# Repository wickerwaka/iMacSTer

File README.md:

# iMacSTer

The iMacSTer is an early 2000's Apple iMac G3 with a MiSTer FPGA multisystem emulator inside of it. It is intended to be a non-destructive modification so the iMac can be returned to it's original state if desired. The mainboard, drives and IO panel are removed and replace by custom hardware, but no cuts are made to the chassis and the new hardware connects to existing internal connections without the need for any soldering. That being said, I can make no guarantees about the long term implications of these modifications. The speakers are being driven by a different amplifier than they were intended for, the new hardware only uses the 5V output from a power supply which is expecting load on the 3.3V and 12V lines also, the monitor is being driven at a resolution higher than it was intended for, heat generation and dissipation characteristics have changed, etc, etc.

## Past Work
None of this would be possible without the work of Rocky Hill and others to reverse engineer the iMac internals and design custom hardware and software to interface with it. I would not have attempted this project if the [imac_g3_ivad_board_init](https://github.com/qbancoffee/imac_g3_ivad_board_init) project did not exist. My PCBs and software is all based on that work and I still use the down converter adaptor board from that project because there was no need to change it.

I also used the IO shield designs that @Diepzeevogel created as part of their [replacement parts project](https://github.com/Diepzeevogel/iMac-G3-replacement-parts) as the basis for my own IO shield. The fit and quality that they were able to achieve is beyond my own skills.

## Features
 * 2W x 2 Stereo amplifier
 * Dual headphone ports for two player fun
 * External volume control
 * 4 external USB ports
 * Built-in WiFi
 * Access to all MiSTer buttons and OSD
 * Sleek design for any modern home

[Other Random Photos](https://photos.app.goo.gl/XmcNqWLyWzHymW5z9)

## Assembly

## Main Board

The main board controls the whole system. It contains an I2S digital-to-analog audio converter, an audio amplifier and an Arduino Nano Every for controlling everything. It connects to the J20 connector inside the iMac which provides 5V to the microcontroller even when the system is powered down. The J20 port is also where the VGA signals are from the VGA connector on the board.

The amplifier is a Texas Instruments [TPA6021A4](https://www.ti.com/lit/ds/symlink/tpa6021a4.pdf) 2W Stereo amplifier. I picked this one because it was in the power range I needed, it supported a headphone mode, the volume level could be controlled by a microcontroller and it came in a through-hole package. That last point really limits the options since most amplifier ICs with similar features come in surface mount packages. When I started this project I had no experience designing PCBs or using surface mount components, so I was limiting myself to through-hole parts. The decoupling, biasing and filtering capacitors in the amplifier section are all directly copied from the reference schematics in the datasheet, with the exception of the output capacitors which I switch from 330uF to 2200uF in order to get more bass.

The amplifier output is connected to the speakers and headphones via two JST connectors. The iMac has two separate headphone ports on the front and each has their own headphone sense signal. These signals need to be OR'd together to determine whether the amplifier should be in single ended (headphone) mode or not. This is done by the arduino rather than a separate IC, which has the added advantage of allowing separate volume settings for speaker and headphone mode.

The audio input to the amplifier comes from the [UDA1334A](https://cdn-shop.adafruit.com/product-files/3678/UDA1334ATS.pdf) [breakout board](https://www.adafruit.com/product/3678) from Adafruit. The UDA1334A decodes the I2S audio data from the MiSTer and converts it to an analog signal. I had assumed the output capacitors on the breakout board would block DC into the amplifier so an earlier version of the board did not have any capacitors protecting the input. That assumption cost me a pair of speakers, they literally ripped themselves apart.

The arduino controls the system power, the CRT configuration, the amplifier, the buttons and LEDs on the case and the three standard buttons on the MiSTer. I considered using an ATmega microcontroller directly instead of the Nano Every, however the Nano packs a lot of features into a small space. I want the convenience of a USB port without having to worry about whether I've hooked it all up correctly. 

iMac video hardware requires a special initialization sequence to be sent via I2C before it will power on the CRT and start displaying an image ([much more detailed explaination here](https://github.com/qbancoffee/imac_g3_ivad_board_init/wiki/Convert-and-iMac-G3-slot-loader-into-a-standard-VGA-monitor)). The I2C connection is also used to configure display properties like brightness and alignment. These settings are stored in EEPROM and can be modified using serial commands.

## USB Hubs

There are two USB hubs inside, one is used for internal connections and one is mounted on the IO shield for external connections. The hub is based on the [FE1.1](https://elinux.org/images/e/ee/FE11-datasheet.pdf) chip which does pretty much everything. Building my own USB hubs is not something I considered doing at the start of this project, I had never designed a PCB and I had never used surface mount components. I had deliberately avoided surface mount components when picking an amplifier for the main board. This seemed achievable though and I had watched enough videos at this point to not be terrified of surface mount soldering. It was pretty surprising when it worked!

The hub includes a current-limited switch, but I have not been able to get the power control from the FE1.1 to work correctly. For now it is latched one with a blob of solder. There is still some current limiting due to the thermal shutoff building into the switch, but it is not going to be reported to the hub correctly.

## MiSTer

The [MiSTer](https://github.com/MiSTer-devel/Main_MiSTer/wiki) setup is the standard combo of DE-10 Nano, 128MB SDRAM and the analog IO board. The 5-pin button and I2S headers are connected to the matching headers on the main board. The MiSTer is mounted in the drive bay alongside one of the USB hubs. I drilled and tapped holes in the drive bay to allow both of them to be mounted. This is a destructive modification, though it is not externally visible and does not impact the functionality of the drive bay if the original drives ever needed to be added back in.

## Power and Front Panel

The power for the system comes from the J22 connector as 24VAC. This 24VAC is feed into the down converter board which outputs 12V, 5V and 3.3V DC. The 5V output is used to power everything else in the system. The J22 connector also has connections for the speakers, headphones, power button and it's LEDs. This are all exposed through three JST connectors on the adaptor board.

## IO Shield

The IO shield provides a mounting point for the external USB hub and the rotary encoder. Thanks to the work [here](https://github.com/Diepzeevogel/iMac-G3-replacement-parts) it matches the curves of the case very closely. It is 3D printed using eSUN's Semi-transparent Gray PETG filament which matches well with the "Graphite" color of this iMac.

The metal plate that the IO shield is attached to has a lot of holes so finding suitable attachment points was not difficult. However getting access to the other side of that metal plate is extremely difficult so I opted to build in some plugs that expand when a bolt is screwed into them, similar to dry wall screws. 

## Video Modes
The CRT in the iMac is limited to a horizontal sync of 57-63KHz. The only mode suitable for 60Hz refresh rate is 1280x960. At this resolution the horizontal refresh rate is 1000x the vertical rate so when using `vsync_adjust` the vertical rate can be adjusted from 57-63Hz, which gives good coverage for NTSC and most arcade systems. The brightness and alignment of the screen does change across that frequency range, so at the extremes the picture will be slightly distorted. A future version of the board may sample the hsync signal and adjust the video settings based on it.

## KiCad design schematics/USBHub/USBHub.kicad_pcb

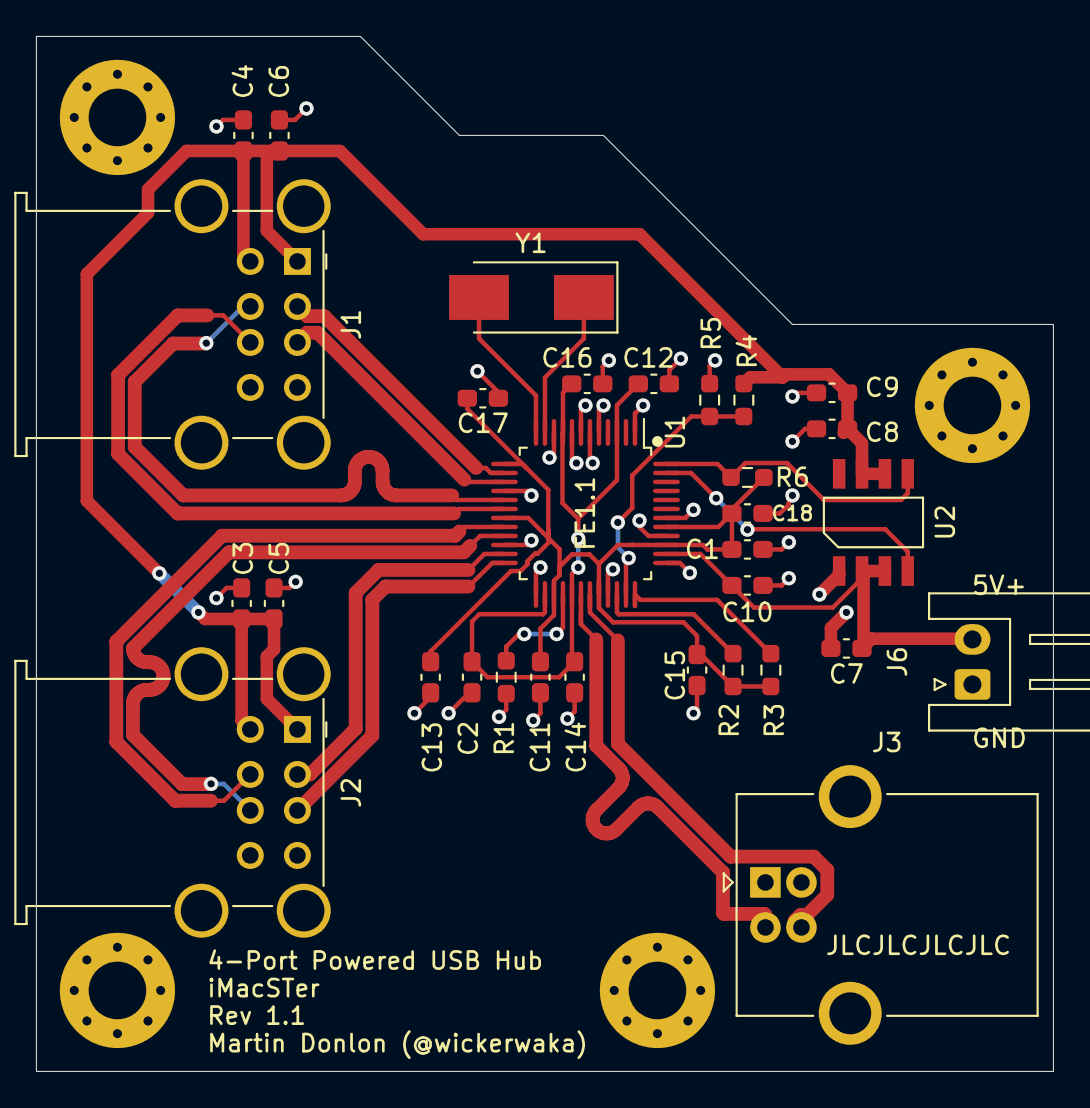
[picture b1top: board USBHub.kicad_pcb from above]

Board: 2 copper layers, 56.5 x 57.5 mm, 35 parts (0 on the bottom side), 23 nets.

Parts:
C1, C2, C3, C4, C5, C6, C9: 10u; C_0603_1608Metric_Pad1.08x0.95mm_HandSolder
C7, C8, C10, C11, C12, C13, C14, C15, C16, C17, C18: 100n; C_0603_1608Metric_Pad1.08x0.95mm_HandSolder
H1, H2, H3, H4: MountingHole_Pad; MountingHole_3.2mm_M3_Pad_Via
J1, J2: USB_A_STACKED; USB_A_Wuerth_61400826021_Horizontal_Stacked
J3: USB_B; USB_B_OST_USB-B1HSxx_Horizontal
J6: Screw_Terminal_01x02; JST_XH_S2B-XH-A_1x02_P2.50mm_Horizontal
R1: 2.7K; R_0603_1608Metric_Pad0.98x0.95mm_HandSolder
R2, R3, R5: 100k; R_0603_1608Metric_Pad0.98x0.95mm_HandSolder
R4: 47k; R_0603_1608Metric_Pad0.98x0.95mm_HandSolder
R6: 10k; R_0603_1608Metric_Pad0.98x0.95mm_HandSolder
U1: FE1.1; FE1_1_QFP48
U2: AP2411; AP24x1_SO8_HandSolder
Y1: 12Mhz; Crystal_SMD_0603-2Pin_6.0x3.5mm_HandSoldering

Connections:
/D1+: J2.3, U1.24
/D1-: J2.2, U1.23
/D2+: J2.7, U1.21
/D2-: J2.6, U1.20
/D3+: J1.7, U1.18
/D3-: J1.6, U1.17
/D4+: J1.3, U1.15
/D4-: J1.2, U1.14
/DU+: J3.3, U1.31
/DU-: J3.2, U1.30
GND: C1.2, C2.2, C3.2, C4.2, C5.2, C6.2, C7.2, C8.2, C9.2, C10.2, C11.2, C12.2, C13.2, C14.2, C15.2, C16.2, C17.2, C18.2, H1.1, H2.1, H3.1, H4.1, J1.4, J1.8, J1.9, J2.4, J2.8, J2.9, J3.4, J3.5, J6.1, R1.2, R5.1, U1.1, U1.5, U1.6, U1.7, U1.8, U1.10, U1.16, U1.22, U1.25, U1.33, U1.37, U1.40, U1.42, U2.1
unnamed: R1.1, U1.28
unnamed: R2.2, U1.34
unnamed: R3.2, U1.36
unnamed: U1.11, Y1.1
unnamed: U1.12, Y1.2
OVER_CURRENT: R6.1, U1.48, U2.5
POWER_EN: U1.47, U2.4
VBUS: C3.1, C4.1, C5.1, C6.1, C8.1, C9.1, J1.1, J1.5, J2.1, J2.5, R4.2, U2.6, U2.7
VBUSM: R4.1, R5.2, U1.35
VD5: C7.1, C10.1, J6.2, U1.38, U2.2, U2.3
VD18: C2.1, C12.1, C14.1, C16.1, U1.3, U1.9, U1.26, U1.29
VD33: C1.1, C11.1, C13.1, C15.1, C17.1, C18.1, R2.1, R3.1, R6.2, U1.13, U1.19, U1.27, U1.32, U1.39, U1.41

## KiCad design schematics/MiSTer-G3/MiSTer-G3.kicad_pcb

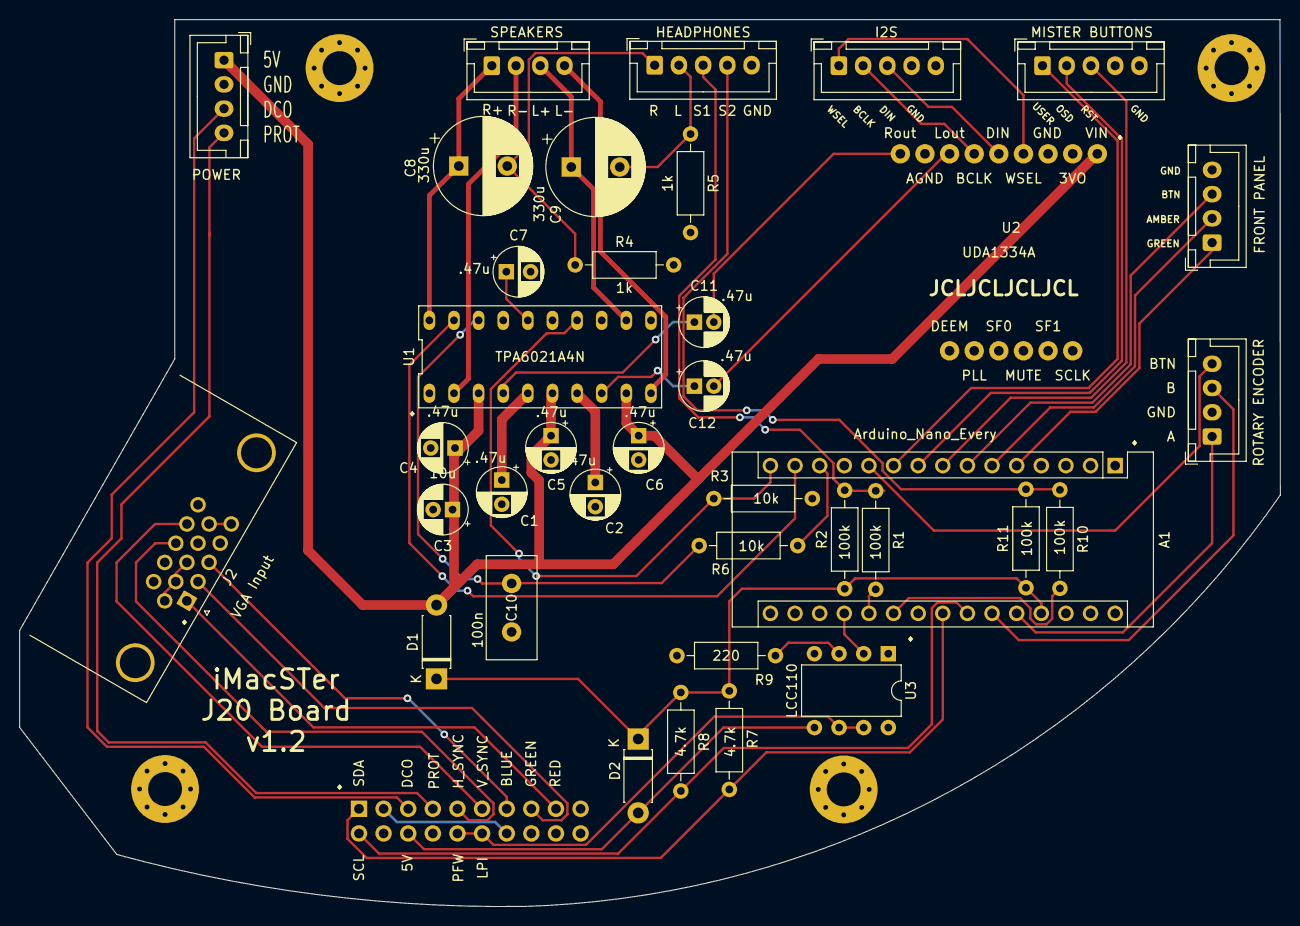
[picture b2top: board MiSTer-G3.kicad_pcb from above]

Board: 2 copper layers, 130.0 x 91.5 mm, 42 parts (1 on the bottom side), 49 nets.

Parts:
A1: Arduino_Nano_Every; Arduino_Nano
C1, C2, C4, C5, C6, C7: .47u; CP_Radial_D5.0mm_P2.50mm
C3: 10u; CP_Radial_D5.0mm_P2.00mm
C8, C9: 330u; CP_Radial_D10.0mm_P5.00mm
C10: 100n; C_Disc_D10.5mm_W5.0mm_P5.00mm
C11, C12: .47u; CP_Radial_D5.0mm_P2.00mm
D1, D2: D_Schottky_ALT; D_DO-41_SOD81_P7.62mm_Horizontal
FRONT PANEL: Front Panel; JST_XH_B4B-XH-A_1x04_P2.50mm_Vertical
H1, H2, H3, H4: MountingHole_Pad; MountingHole_3.5mm_Pad_Via
HEADPHONES: Headphones; JST_XH_B5B-XH-A_1x05_P2.50mm_Vertical
J1: Apple J20; PinHeader_2x10_P2.54mm_Vertical
J2: VGA Input; DSUB-15-HD_Female_Horizontal_P2.29x1.98mm_EdgePinOffset8.35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
J4: I2S; JST_XH_B5B-XH-A_1x05_P2.50mm_Vertical
MISTER BUTTONS: Buttons; JST_XH_B5B-XH-A_1x05_P2.50mm_Vertical
POWER: Power; JST_XH_B4B-XH-A_1x04_P2.50mm_Vertical
R1, R2, R10, R11: 100k; R_Axial_DIN0207_L6.3mm_D2.5mm_P10.16mm_Horizontal
R3, R6: 10k; R_Axial_DIN0207_L6.3mm_D2.5mm_P10.16mm_Horizontal
R4, R5: 1k; R_Axial_DIN0207_L6.3mm_D2.5mm_P10.16mm_Horizontal
R7, R8: 4.7k; R_Axial_DIN0207_L6.3mm_D2.5mm_P10.16mm_Horizontal
R9: 220; R_Axial_DIN0207_L6.3mm_D2.5mm_P10.16mm_Horizontal
ROTARY ENCODER: Rotary Encoder; JST_XH_B4B-XH-A_1x04_P2.50mm_Vertical
SPEAKERS: Speaker; JST_XH_B4B-XH-A_1x04_P2.50mm_Vertical
U1: TPA6021A4N; TPA6021A4
U2: UDA1334A; UDA1334_Breakout
U3: LCC110; DIP-8_W7.62mm

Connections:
5V_MCU: A1.27, D1.1, D2.1, R2.1, R7.2, R8.1, R11.1
5V_PSU: C3.1, C4.1, C5.1, C6.1, D1.2, POWER.1, U1.3, U1.6, U1.9, U2.1
5V_TRICKLE: D2.2, J1.6, U3.5
AMBER_LED: A1.6, FRONT PANEL.2
AMP_ACTIVE: A1.15, R3.1, U1.14
AMP_SE: A1.14, U1.19
BLUE: J1.13, J2.3
BTN_OSD: A1.9, MISTER BUTTONS.2
BTN_RESET: A1.8, MISTER BUTTONS.3
BTN_USER: A1.10, MISTER BUTTONS.1
DCO: J1.5, POWER.3
GND: A1.4, A1.29, C1.2, C2.2, C3.2, C4.2, C5.2, C6.2, C7.2, C10.2, FRONT PANEL.4, H1.1, H2.1, H3.1, H4.1, HEADPHONES.5, J1.3, J1.4, J1.14, J1.16, J1.18, J1.20, J2.5, J2.6, J2.7, J2.8, J2.10, J4.4, MISTER BUTTONS.5, POWER.2, R3.2, R4.2, R5.2, R9.1, ROTARY ENCODER.2, U1.1, U1.11, U1.15, U1.17, U2.3, U2.8, U3.8
GREEN: J1.15, J2.2
GREEN_LED: A1.5, FRONT PANEL.1
H_SYNC: J1.9, J2.13
I2S_BCLK: J4.2, U2.6
I2S_DIN: J4.3, U2.5
I2S_WSEL: J4.1, U2.4
IVAD_SCL: A1.24, J1.2, R8.2
IVAD_SDA: A1.23, J1.1, R7.1
LHEAD: C9.2, HEADPHONES.2, R5.1
LIN: C12.2, U2.7
LPIACT: J1.10, J1.12, U3.6, U3.7
LSPKR+: C9.1, SPEAKERS.3, U1.12
LSPKR-: SPEAKERS.4, U1.10
unnamed: A1.13, R6.1
unnamed: C1.1, U1.5
unnamed: C2.1, U1.7
unnamed: C7.1, U1.16
unnamed: C11.1, U1.4
unnamed: C12.1, U1.8
unnamed: R9.2, U3.3
POWER_BTN: A1.7, FRONT PANEL.3
POWER_EN: A1.19, U3.2
PROT: J1.7, POWER.4
RED: J1.17, J2.1
RHEAD: C8.2, HEADPHONES.1, R4.1
RIN: C11.2, U2.9
ROT_A: A1.26, ROTARY ENCODER.1
ROT_B: A1.25, ROTARY ENCODER.3
ROT_BTN: A1.11, ROTARY ENCODER.4
RSPKR+: C8.1, SPEAKERS.1, U1.20
RSPKR-: SPEAKERS.2, U1.2
SHEAD1: HEADPHONES.3, R1.1, R2.2
SHEAD2: HEADPHONES.4, R10.1, R11.2
VOLUME: C10.1, R6.2, U1.18
V_SYNC: J1.11, J2.14
~HEAD_DETECT1: A1.20, R1.2
~HEAD_DETECT2: A1.21, R10.2

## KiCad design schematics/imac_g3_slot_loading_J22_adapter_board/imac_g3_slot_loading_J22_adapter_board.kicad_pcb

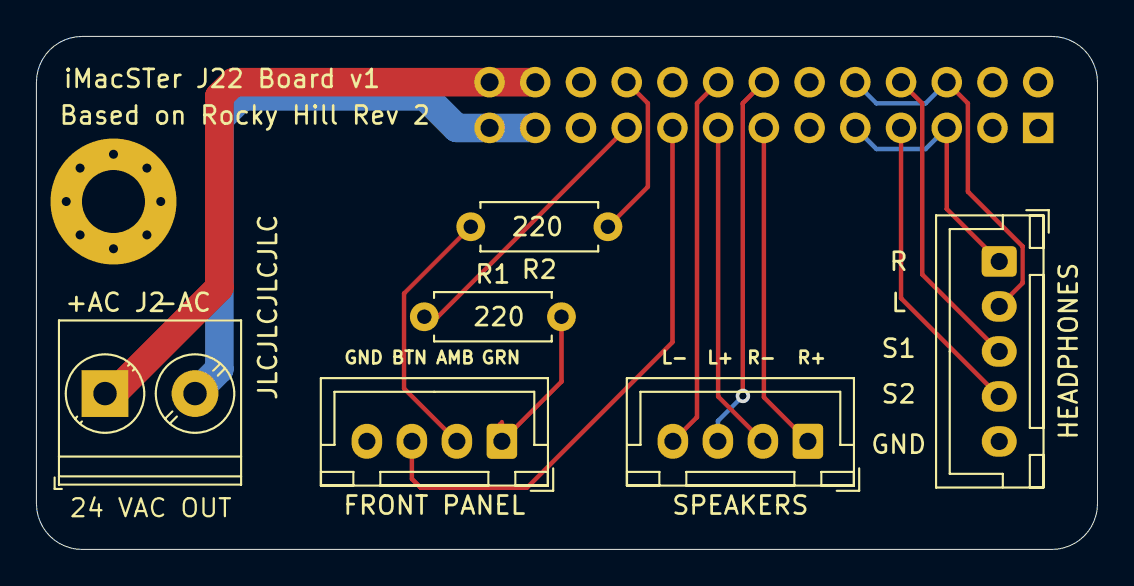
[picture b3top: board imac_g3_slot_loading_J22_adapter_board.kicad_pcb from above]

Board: 2 copper layers, 58.9 x 28.5 mm, 8 parts (1 on the bottom side), 16 nets.

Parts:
FRONT PANEL: Conn_01x04_Male; JST_XH_B4B-XH-A_1x04_P2.50mm_Vertical
H1: MountingHole_Pad; MountingHole_3.5mm_Pad_Via
HEADPHONES: Conn_01x04_Male; JST_XH_B5B-XH-A_1x05_P2.50mm_Vertical
J1: Conn_02x13_Odd_Even; PinHeader_2x13_P2.54mm_Vertical
J2: AC Power; TerminalBlock_Phoenix_PT-1,5-2-5.0-H_1x02_P5.00mm_Horizontal
R1, R2: 220; R_Axial_DIN0207_L6.3mm_D2.5mm_P7.62mm_Horizontal
SPEAKERS: Conn_01x04_Male; JST_XH_B4B-XH-A_1x04_P2.50mm_Vertical

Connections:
/+AC: J1.24, J1.26, J2.1
/+AMBER_LED: J1.20, R2.1
/+GREEN_LED: J1.19, R1.1
/+LEFT_SPEAKER: J1.14, SPEAKERS.3
/+RIGHT_SPEAKER: J1.13, SPEAKERS.1
/-AC: J1.23, J1.25, J2.2
/-LEFT_SPEAKER: J1.16, SPEAKERS.4
/-RIGHT_SPEAKER: J1.15, SPEAKERS.2
/HEADPHONE_1_LEFT: HEADPHONES.2, J1.6, J1.10
/HEADPHONE_1_RIGHT: HEADPHONES.1, J1.5, J1.9
/HEADPHONE_1_SENSE: HEADPHONES.3, J1.8
/HEADPHONE_2_SENSE: HEADPHONES.4, J1.7
/POWER_BUTTON: FRONT PANEL.3, J1.17
GNDREF: FRONT PANEL.4, H1.1, HEADPHONES.5, J1.4, J1.11, J1.18
unnamed: FRONT PANEL.1, R1.2
unnamed: FRONT PANEL.2, R2.2

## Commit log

2021-07-11 Controller code
2021-07-11 gitignore
2021-07-11 Schematics
2021-07-14 Headers and routing
    Added JST header for mister buttons
    Split screw terminals into separate JST headers for speakers, headphones and front panel.
    Added rotary encoder button
    Re-routed pcb
2021-07-17 Fixed up USBHub symbol and footprint library
2021-07-18 Update LICENSE
    Change to LGPLv3 to match the imac_g3_ivad_board_init project
2021-07-21 Schematic changes
    Reworked Rocky Hills j22 adaptor, removed microphone, added JST headers for speakers, buttons and headphones.
    Updated USBHub for FE1.1 5V doesn't go through the current limiting switch
2021-07-25 Headphone sense
    Added second sense wire from j22 board since they can't be combined.
    Send sense inputs to arduino and control SE/~BTL signal from there. This will allow different volume settings for each mode.
    Re-route.
    Fix silkscreen labels
2021-07-28 Updated todo
2021-08-15 Code and schematic changes
    Fixed incorrect routing for decoupling caps
    Updated code to handle headphones, power button and mister buttons.
2021-08-16 USBHub
    Added 3d models for usb connectors
    Exported a 3d model for the whole hub
    Changed the power connector to a horizontal one, not sure if that's what I'll use yet.
2021-08-25 Jekyll dummy site
2021-08-25 Fixed urls
2021-08-27 Update the readme
2021-08-27 Fixed some typos. Added google photo link.
2021-08-27 Fix links
2021-08-27 Added two additional images
2021-08-27 Added 3d printing models
2023-02-02 Gerber Files
    Exported gerber files for all PCBs
    Updated main board to version 1.2 with fixes the routing that were bodged into previous version.
    Updated to kicad 6
2023-02-23 Update part numbers
2023-02-23 Added missing csv files
